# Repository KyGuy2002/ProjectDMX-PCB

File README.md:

PCB designs for projectdmx.us modular prop controller

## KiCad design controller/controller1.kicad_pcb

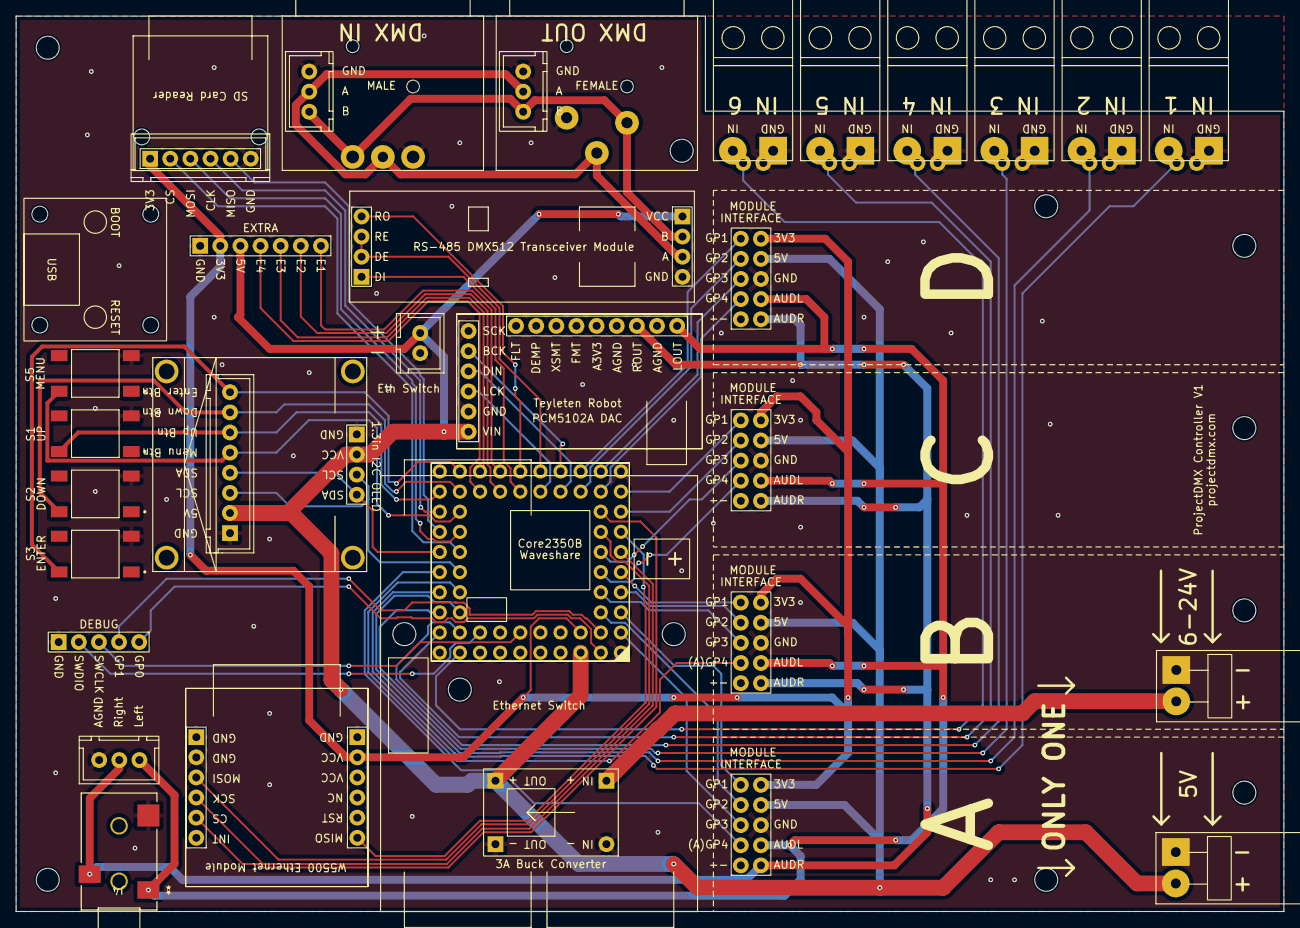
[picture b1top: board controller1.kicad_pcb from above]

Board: 2 copper layers, 160.0 x 113.0 mm, 31 parts (0 on the bottom side), 57 nets.

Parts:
J2: Female XLR Out; AC3FAH-AU-PRE_AMP
J3: Male XLR In; AC3MAH-AU-PRE_AMP
J4: SJ-3523-SMT; SJ-3523-SMT-TR
S1: UP; SW_TS04-66-43-BK-260-SMT
S2: DOWN; SW_TS04-66-43-BK-260-SMT
S3: ENTER; SW_TS04-66-43-BK-260-SMT
S5: MENU; SW_TS04-66-43-BK-260-SMT
U1: Waveshare RP2350B
U2: DMX Transceiver
U4: JST XH Power
U5: OLED 1_3in I2C
U6, U7, U13, U14: Module Interface
U8: Tey PCM DAC
U9: SD Card Reader
U10: W5500 Ethernet Module
U11: 3A Buck Converter
U12: Debug Header
U15, U17, U18, U19, U20, U21: Horiz Terminal Block
U16: Extra Header
U26: Interface Connector
U27, U28: DMX Alt JST
U29: Aux Alt JST

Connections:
3V3: U1.13 (3V3), U6.0, U7.0, U9.6 (3V3), U10.5 (3V3), U13.0, U14.0, U16.6 (3V)
5V: U1.3 (VBUS), U2.4 (VCC), U4.2 (GND), U5.3 (VCC), U6.4 (AGP4), U7.4 (AGP4), U8.6 (VIN), U11.1 (OUT_+), U13.4 (AGP4), U14.4 (AGP4), U16.5 (5V), U26.2 (5V)
GND: J2.1, J3.1, J4.2, S1.2, S2.2, S3.2, S5.2, U1.1 (GND), U1.10 (GND), U1.36 (GND), U1.55 (GND), U2.3 (GND), U4.1 (VCC), U5.4 (GND), U6.3 (GP3), U7.3 (GP3), U8.1 (SCK), U8.5 (GND), U9.1 (GND), U10.6 (GND), U10.11 (GND), U10.12 (GND), U11.2 (OUT_-), U11.4 (IN_-), U12.5 (GND), U13.3 (GP3), U14.3 (GP3), U15.2 (GND), U16.7 (GND), U17.2 (GND), U18.2 (GND), U19.2 (GND), U20.2 (GND), U21.2 (GND), U26.1 (GND), U27.1 (GND), U28.1 (GND), U29.1 (AGND)
GP7: U1.27 (GP7), U13.6 (5V)
unnamed: U1.62 (AGP40), U6.6 (5V)
unnamed: U1.64 (AGP41), U7.6 (5V)
unnamed: U1.65 (AGP42), U21.1 (IN)
unnamed: U1.67 (AGP43), U20.1 (IN)
unnamed: U1.66 (AGP44), U19.1 (IN)
unnamed: U1.20 (AGP45), U17.1 (IN)
unnamed: U1.19 (AGP46), U18.1 (IN)
unnamed: U1.9 (AGP47), U15.1 (IN)
unnamed: U1.2 (GP0), U12.1 (GP0)
unnamed: U1.12 (GP1), U12.2 (GP1)
unnamed: U1.11 (GP2), U6.7 (GND)
unnamed: U1.23 (GP3), U6.8
unnamed: U1.21 (GP4), U6.9
unnamed: U1.25 (GP5), U7.7 (GND)
unnamed: U1.24 (GP6), U7.8
unnamed: U1.26 (GP8), U7.9
unnamed: U1.29 (GP9), U13.7 (GND)
unnamed: U1.28 (GP10), U10.9 (SCLK)
unnamed: U1.31 (GP11), U10.10 (MOSI)
unnamed: U1.30 (GP12), U10.1 (MISO)
unnamed: U1.33 (GP13), U10.8 (CS)
unnamed: U1.32 (GP14), U13.8
unnamed: U1.34 (GP15), U13.9
unnamed: U1.35 (GP16), U14.6 (5V)
unnamed: U1.37 (GP17), U14.7 (GND)
unnamed: U1.38 (GP18), U14.8
unnamed: U1.39 (GP19), U14.9
unnamed: U1.41 (GP20), U8.3 (DIN)
unnamed: U1.40 (GP21), U8.2 (BCK)
unnamed: U1.42 (GP22), U8.4 (LCK)
unnamed: U1.44 (GP23), U2.2 (DE), U2.8 (RE)
unnamed: U1.46 (GP24), U2.1 (DI)
unnamed: U1.45 (GP25), U2.7 (RO)
unnamed: U1.48 (GP26), U16.2 (E2)
unnamed: U1.47 (GP27), U16.1 (E1)
unnamed: U1.49 (GP28), U16.4 (E4)
unnamed: U1.50 (GP29), U16.3 (E3)
unnamed: S3.3, U1.51 (GP30), U26.8 (Enter_Btn)
unnamed: S2.3, U1.52 (GP31), U26.7 (Down_Btn)
unnamed: S1.3, U1.53 (GP32), U26.6 (Up_Btn)
unnamed: S5.3, U1.56 (GP33), U26.5 (Menu_Btn)
unnamed: U1.57 (GP34), U9.3 (CLK)
unnamed: U1.59 (GP35), U9.4 (MOSI)
unnamed: U1.58 (GP36), U9.2 (MISO)
unnamed: U1.60 (GP37), U9.5 (CS)
unnamed: U1.61 (GP38), U5.1 (SDA), U26.4 (SDA)
unnamed: U1.63 (GP39), U5.2 (SCL), U26.3 (SCL)
unnamed: U1.16 (SWCLK), U12.3 (SWCLK)
unnamed: U1.18 (SWDIO), U12.4 (SWDIO)
unnamed: J2.3, J3.3, U2.5 (A), U27.2 (A), U28.2 (A)
unnamed: J2.2, J3.2, U2.6 (B), U27.3 (B), U28.3 (B)
unnamed: J4.1, U6.2 (GP2), U7.2 (GP2), U8.15 (LROUT), U13.2 (GP2), U14.2 (GP2), U29.3 (R)
unnamed: J4.3, U6.1 (GP1), U7.1 (GP1), U8.13 (ROUT), U13.1 (GP1), U14.1 (GP1), U29.2 (L)

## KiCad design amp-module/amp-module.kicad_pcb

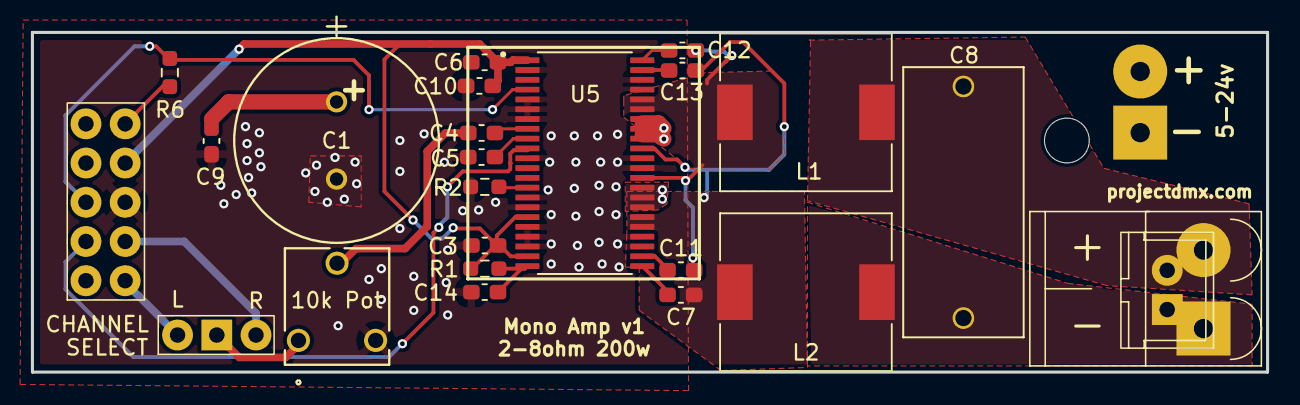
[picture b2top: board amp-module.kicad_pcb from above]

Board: 2 copper layers, 80.0 x 22.0 mm, 22 parts (0 on the bottom side), 16 nets.

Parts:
C1: 1000uf; 35YXJ1000M12.5X20
C3, C14: 1uF CER 25v; C_0603_1608Metric_Pad1.08x0.95mm_HandSolder
C4, C5: 10uF CER 25v; C_0603_1608Metric_Pad1.08x0.95mm_HandSolder
C6: 100nF; C_0603_1608Metric_Pad1.08x0.95mm_HandSolder
C7, C12, C13: 33nF CER 50v; C_0603_1608Metric_Pad1.08x0.95mm_HandSolder
C8: 1uf ECW Film; ECWFD2W105J
C9: 1uf GMK316BJ105KL 100v; C_0603_1608Metric_Pad1.08x0.95mm_HandSolder
C10: 10uF; C_0603_1608Metric_Pad1.08x0.95mm_HandSolder
C11: 33nf CER 50v; C_0603_1608Metric_Pad1.08x0.95mm_HandSolder
L1, L2: 7443331000
R1: 3.3Ω; R_0603_1608Metric_Pad0.98x0.95mm_HandSolder
R2: 30kΩ; R_0603_1608Metric_Pad0.98x0.95mm_HandSolder
R6: 10kΩ; R_0603_1608Metric_Pad0.98x0.95mm_HandSolder
U2: Vert Terminal Block p2
U3: 2p Output
U5: TPA3221DDVR; TPA3221
U6: PSU Select Jumper

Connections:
5V: C3.2, C6.2, C10.2, R1.1, U5.1 (VDD), U5.17 (CMUTE), U5.21 (AVDD)
GND: C1.2, C3.1, C5.2, C6.1, C9.2, C10.1, C14.1, R2.2, U5.2 (GAIN/SLV), U5.5 (GND-11), U5.6 (GND-5), U5.7 (GND-4), U5.11 (HEAD), U5.15 (IN2_P), U5.16 (IN2_M), U5.18 (GND-1), U5.19 (GND), U5.20 (GND-10), U5.25 (GND-6), U5.26 (GND-2), U5.33 (GND-3), U5.34 (GND-8), U5.41 (GND-9), U5.42 (GND-7)
unnamed: R6.2, U5.4 (FAULT)
unnamed: C8.2, L1.1, U2.1 (+), U3.1 (+)
unnamed: C8.1, L2.1, U2.2 (-), U3.2 (-)
unnamed: C13.1, U5.43 (BST1_M)
unnamed: C12.2, U5.44 (BST1_P)
unnamed: C7.2, U5.23 (BST2_M)
unnamed: C11.1, U5.24 (BST2_P)
unnamed: R2.1, U5.14 (FREQ_ADJ)
unnamed: C14.2, R1.2, U5.22 (GVDD)
unnamed: C5.1, U5.9 (IN1_M)
unnamed: C4.2, U5.8 (IN1_P)
unnamed: C7.1, C13.2, L2.2, U5.27 (OUT2_M), U5.28 (OUT2_M-1), U5.35 (OUT1_M)
unnamed: C11.2, C12.1, L1.2, U5.32 (OUT2_P), U5.39 (OUT1_P), U5.40 (OUT1_P-1)
VCC: C1.1, C9.1, U5.29 (PVDD-4), U5.30 (PVDD-5), U5.31 (PVDD-3), U5.36 (PVDD-2), U5.37 (PVDD-1), U5.38 (PVDD)

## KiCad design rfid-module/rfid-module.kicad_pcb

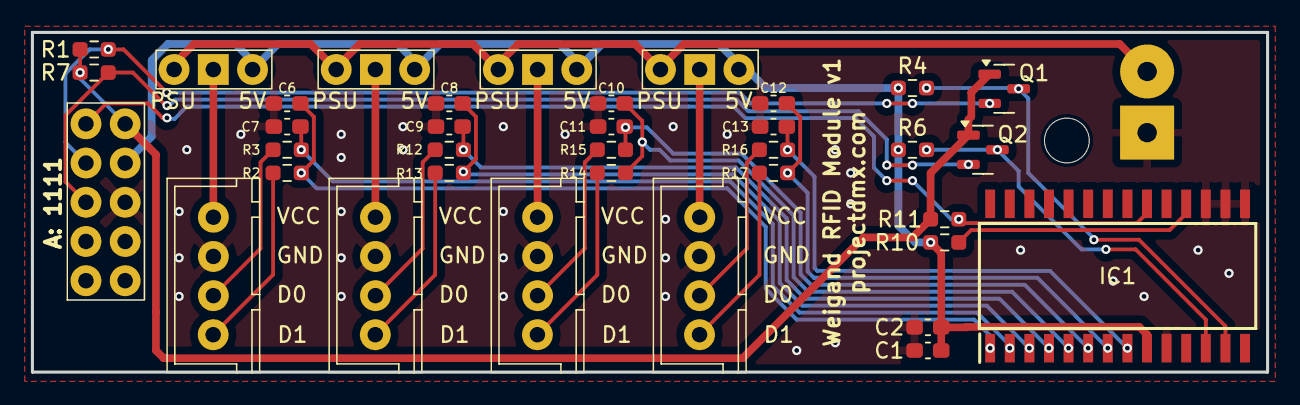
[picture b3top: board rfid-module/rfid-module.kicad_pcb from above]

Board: 2 copper layers, 80.0 x 22.0 mm, 35 parts (0 on the bottom side), 30 nets.

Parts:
C1: 100nF; C_0603_1608Metric_Pad1.08x0.95mm_HandSolder
C2: 10uF; C_0603_1608Metric_Pad1.08x0.95mm_HandSolder
C6, C7, C8, C9, C10, C11, C12, C13: 1nF; C_0603_1608Metric_Pad1.08x0.95mm_HandSolder
IC1: MCP23017-E_SO; MCP23017
Q1, Q2: BSS138; SOT-23
R1, R4, R6, R7, R11: 4.7kΩ; R_0603_1608Metric_Pad0.98x0.95mm_HandSolder
R2, R3, R12, R13, R14, R15, R16, R17: 1kΩ; R_0603_1608Metric_Pad0.98x0.95mm_HandSolder
R10: 10kΩ; R_0603_1608Metric_Pad0.98x0.95mm_HandSolder
U2, U5, U7, U9: RFID JST
U3, U4, U6, U8: RFID PSU Select

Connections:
3V3: Q1.1 (G), Q2.1 (G), R1.1, R7.1, R11.1
5V: C1.2, C2.2, IC1.9 (VDD), R4.1, R6.1, R10.1, U3.1 (5V), U4.1 (5V), U6.1 (5V), U8.1 (5V)
12V: U3.3 (PSU), U4.3 (PSU), U6.3 (PSU), U8.3 (PSU)
GND: C1.1, C2.1, C6.1, C7.1, C8.1, C9.1, C10.1, C11.1, C12.1, C13.1, IC1.10 (VSS), IC1.15 (A0), IC1.16 (A1), IC1.17 (A2), U2.2 (GND), U5.2 (GND), U7.2 (GND), U9.2 (GND)
unnamed: C6.2, IC1.1 (GPB0), R2.2
unnamed: C7.2, IC1.2 (GPB1), R3.2
unnamed: C8.2, IC1.3 (GPB2), R13.2
unnamed: C9.2, IC1.4 (GPB3), R12.2
unnamed: C10.2, IC1.5 (GPB4), R14.2
unnamed: C11.2, IC1.6 (GPB5), R15.2
unnamed: C12.2, IC1.7 (GPB6), R17.2
unnamed: C13.2, IC1.8 (GPB7), R16.2
unnamed: IC1.20 (INTA), R11.2
unnamed: IC1.12 (SCL), Q2.3 (D), R6.2
unnamed: IC1.13 (SDA), Q1.3 (D), R4.2
unnamed: IC1.18 (~RESET), R10.2
unnamed: Q1.2 (S), R1.2
unnamed: Q2.2 (S), R7.2
unnamed: R3.1, U2.3 (D0)
unnamed: R2.1, U2.4 (D1)
unnamed: U2.1 (VCC), U3.2 (OUT)
unnamed: U4.2 (OUT), U5.1 (VCC)
unnamed: R12.1, U5.3 (D0)
unnamed: R13.1, U5.4 (D1)
unnamed: U6.2 (OUT), U7.1 (VCC)
unnamed: R15.1, U7.3 (D0)
unnamed: R14.1, U7.4 (D1)
unnamed: U8.2 (OUT), U9.1 (VCC)
unnamed: R16.1, U9.3 (D0)
unnamed: R17.1, U9.4 (D1)

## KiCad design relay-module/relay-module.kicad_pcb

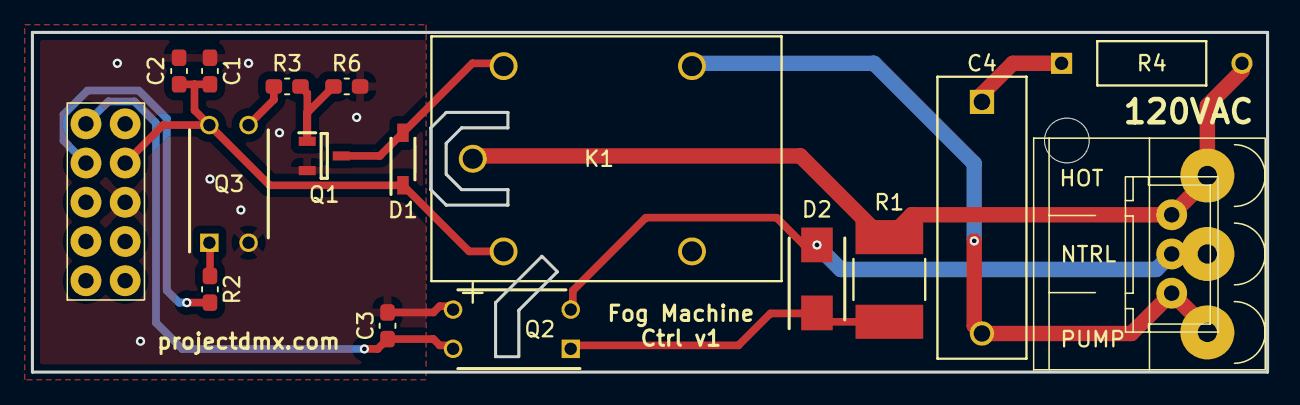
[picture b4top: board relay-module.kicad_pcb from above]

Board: 2 copper layers, 80.0 x 22.0 mm, 17 parts (0 on the bottom side), 12 nets.

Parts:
C1: 100nF; C_0603_1608Metric_Pad1.08x0.95mm_HandSolder
C2, C3: 10uF; C_0603_1608Metric_Pad1.08x0.95mm_HandSolder
C4: C; PHE840EB6100KB05R17
D1: M7; 1N4148W
D2: M7; S1M
K1: SRD-05VDC-SL-C; G5LE_14_DC5
Q1: SOT95P240X115-3N; S8050
Q2, Q3: DIP762W60P254L460H450Q4N; PC817X2NSZ9F
R1: 47kΩ; 354047KFT
R2: 220Ω; C_0603_1608Metric_Pad1.08x0.95mm_HandSolder
R3: 1kΩ; C_0603_1608Metric_Pad1.08x0.95mm_HandSolder
R4: R; FMP100JR-52-100R
R6: 10kΩ; C_0603_1608Metric_Pad1.08x0.95mm_HandSolder
U2: Vert Terminal Block p3
U4: DMX Alt JST

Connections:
5V: C1.2, C2.2, D1.1, K1.2 (C1), Q3.4 (COLLECTOR)
GND: C1.1, C2.1, C3.2, Q1.2 (E), Q2.3 (EMITTER), Q3.2 (CATHODE), R6.1
unnamed: C4.1, R4.1
unnamed: D1.2, K1.5 (NC), Q1.3 (C)
unnamed: K1.1 (COM), R1.1, R4.2, U2.1 (Hot), U4.3 (Hot)
unnamed: C4.2, K1.4 (NO), U2.3 (Pump), U4.1 (Pump)
unnamed: Q1.1 (B), R3.1, R6.2
unnamed: D2.1, Q2.1 (ANODE), R1.2
unnamed: D2.2, Q2.2 (CATHODE), U2.2 (Neutral), U4.2 (Neutral)
unnamed: C3.1, Q2.4 (COLLECTOR)
unnamed: Q3.1 (ANODE), R2.1
unnamed: Q3.3 (EMITTER), R3.2

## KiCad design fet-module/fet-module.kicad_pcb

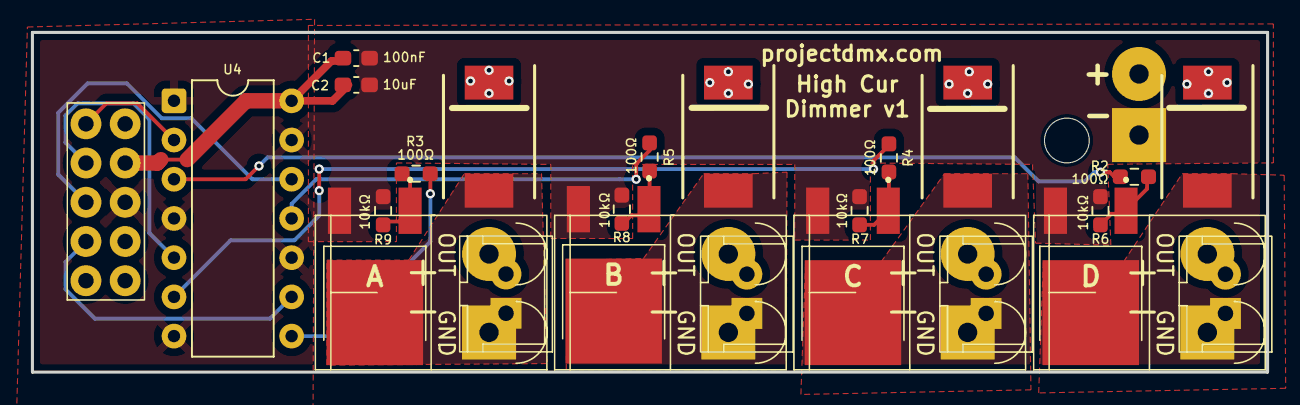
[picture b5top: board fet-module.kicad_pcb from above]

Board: 2 copper layers, 80.0 x 22.0 mm, 27 parts (0 on the bottom side), 11 nets.

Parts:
A: SK1045; SK1045-LTP
A#2: AOD4184A; AOD4185A
B: SK1045; SK1045-LTP
B#2: AOD4184A; AOD4185A
C: AOD4184A; AOD4185A
C1: 100nF; C_0603_1608Metric_Pad1.08x0.95mm_HandSolder
C2: 10uF; C_0603_1608Metric_Pad1.08x0.95mm_HandSolder
C#2: SK1045; SK1045-LTP
D: SK1045; SK1045-LTP
D#2: AOD4184A; AOD4185A
R2, R3, R4, R5: 100Ω; R_0603_1608Metric_Pad0.98x0.95mm_HandSolder
R6, R7, R8, R9: 10kΩ; R_0603_1608Metric_Pad0.98x0.95mm_HandSolder
U1, U6, U8, U10: JST XH Power
U2, U3, U7, U9: Vert Terminal Block p2
U4: DIP-14_W7.62mm

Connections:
5V: C1.2, C2.2, U4.14 (VCC)
GND: A#2.3 (S), B#2.3 (S), C.3 (S), C1.1, C2.1, D#2.3 (S), R6.1, R7.1, R8.1, R9.1, U4.1 (1_OE), U4.4 (2_OE), U4.7 (3_OE), U4.10 (4_OE), U4.13 (GND)
HIGH-A: A.2, A#2.2 (D), U7.2 (-), U8.1 (+)
HIGH-B: B.2, B#2.2 (D), U3.2 (-), U6.1 (+)
HIGH-C: C.2 (D), C#2.2, U1.1 (+), U2.2 (-)
HIGH-D: D.2, D#2.2 (D), U9.2 (-), U10.1 (+)
unnamed: D#2.1 (G), R2.1, R2.2, R6.2, U4.3 (1Y_(Out))
unnamed: A#2.1 (G), R3.1, R3.2, R9.2, U4.8 (3A_(In))
unnamed: C.1 (G), R4.1, R4.2, R7.2, U4.6 (2Y_(Out))
unnamed: B#2.1 (G), R5.1, R5.2, R8.2, U4.11 (4A_(In))
VCC: A.1, B.1, C#2.1, D.1, U1.2 (-), U2.1 (+), U3.1 (+), U6.2 (-), U7.1 (+), U8.2 (-), U9.1 (+), U10.2 (-)

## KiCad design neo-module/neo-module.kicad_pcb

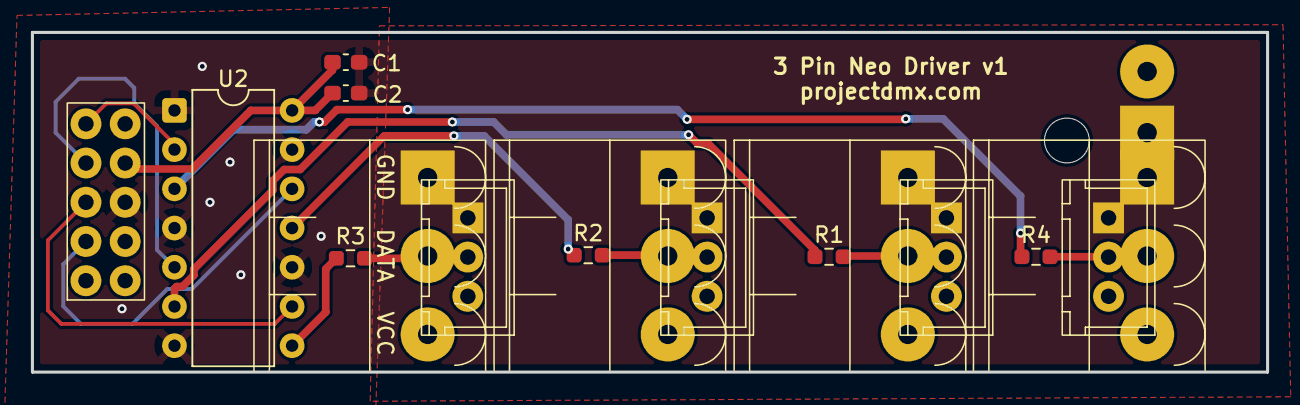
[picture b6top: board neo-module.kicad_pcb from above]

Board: 2 copper layers, 80.0 x 22.0 mm, 7 parts (0 on the bottom side), 6 nets.

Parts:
C1: 100nF; C_0603_1608Metric_Pad1.08x0.95mm_HandSolder
C2: 10uF; C_0603_1608Metric_Pad1.08x0.95mm_HandSolder
R1, R2, R3, R4: 330Ω; R_0603_1608Metric_Pad0.98x0.95mm_HandSolder
U2: DIP-14_W7.62mm

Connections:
5V: C1.2, C2.2, U2.14 (VCC)
GND: C1.1, C2.1, U2.1 (1_OE), U2.4 (2_OE), U2.7 (3_OE), U2.10 (4_OE), U2.13 (GND)
unnamed: R3.1, R3.2, U2.8 (3A_(In))
unnamed: R2.1, R2.2, U2.11 (4A_(In))
unnamed: R1.1, R1.2, U2.6 (2Y_(Out))
unnamed: R4.1, R4.2, U2.3 (1Y_(Out))

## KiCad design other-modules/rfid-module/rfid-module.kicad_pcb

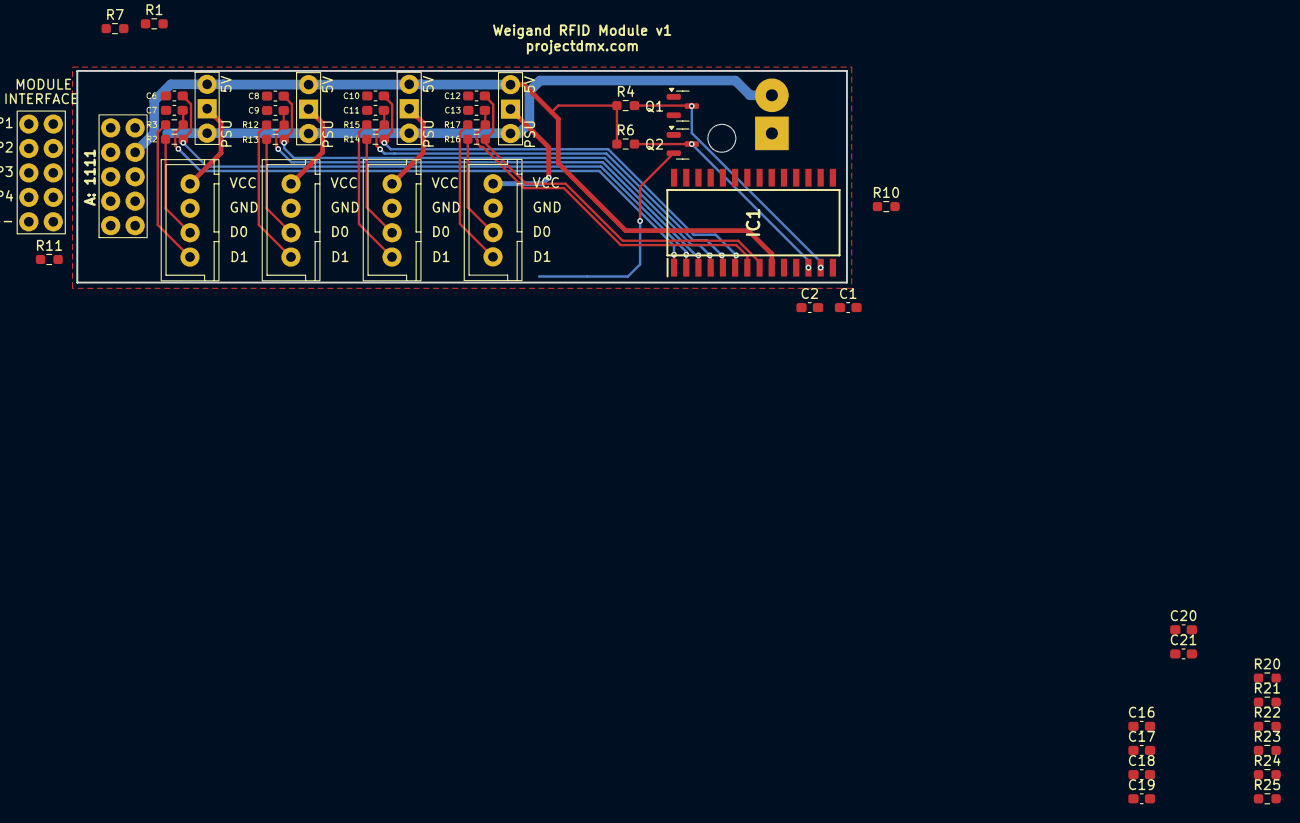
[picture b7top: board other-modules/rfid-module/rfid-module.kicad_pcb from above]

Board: 2 copper layers, 80.0 x 22.0 mm, 48 parts (0 on the bottom side), 36 nets.

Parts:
C1: 100nF; C_0603_1608Metric_Pad1.08x0.95mm_HandSolder
C2: 10uF; C_0603_1608Metric_Pad1.08x0.95mm_HandSolder
C6, C7, C8, C9, C10, C11, C12, C13, C16, C17, C18, C19, C20, C21: 1nF; C_0603_1608Metric_Pad1.08x0.95mm_HandSolder
IC1: MCP23017-E_SO; MCP23017
Q1, Q2: BSS138; SOT-23
R1, R4, R6, R7, R11: 4.7kΩ; R_0603_1608Metric_Pad0.98x0.95mm_HandSolder
R2, R3, R12, R13, R14, R15, R16, R17, R20, R21, R22, R23, R24, R25: 1kΩ; R_0603_1608Metric_Pad0.98x0.95mm_HandSolder
R10: 10kΩ; R_0603_1608Metric_Pad0.98x0.95mm_HandSolder
U1: Module Interface
U2, U5, U7, U9: RFID JST
U3, U4, U6, U8: RFID PSU Select

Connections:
3V3: Q1.1 (G), Q2.1 (G), R1.1, R7.1, R11.1
5V: C1.2, C2.2, IC1.9 (VDD), R4.1, R6.1, R10.1, U1.6 (5V), U3.1 (5V), U4.1 (5V), U6.1 (5V), U8.1 (5V)
12V: U3.3 (PSU), U4.3 (PSU), U6.3 (PSU), U8.3 (PSU)
GND: C1.1, C2.1, C6.1, C7.1, C8.1, C9.1, C10.1, C11.1, C12.1, C13.1, C16.1, C17.1, C18.1, C19.1, C20.1, C21.1, IC1.10 (VSS), IC1.15 (A0), IC1.16 (A1), IC1.17 (A2), U1.7 (GND), U2.2 (GND), U5.2 (GND), U7.2 (GND), U9.2 (GND)
unnamed: C21.2, IC1.21 (GPA0), R25.2
unnamed: C20.2, IC1.22 (GPA1), R24.2
unnamed: C19.2, IC1.23 (GPA2), R23.2
unnamed: C18.2, IC1.24 (GPA3), R22.2
unnamed: C17.2, IC1.25 (GPA4), R21.2
unnamed: C16.2, IC1.26 (GPA5), R20.2
unnamed: C7.2, IC1.1 (GPB0), R3.2
unnamed: C6.2, IC1.2 (GPB1), R2.2
unnamed: C9.2, IC1.3 (GPB2), R12.2
unnamed: C8.2, IC1.4 (GPB3), R13.2
unnamed: C11.2, IC1.5 (GPB4), R15.2
unnamed: C10.2, IC1.6 (GPB5), R14.2
unnamed: C13.2, IC1.7 (GPB6), R17.2
unnamed: C12.2, IC1.8 (GPB7), R16.2
unnamed: IC1.20 (INTA), R11.2, U1.1 (GP1)
unnamed: IC1.12 (SCL), Q2.3 (D), R6.2
unnamed: IC1.13 (SDA), Q1.3 (D), R4.2
unnamed: IC1.18 (~RESET), R10.2
unnamed: Q1.2 (S), R1.2, U1.2 (GP2)
unnamed: Q2.2 (S), R7.2, U1.3 (GP3)
unnamed: R2.1, U2.3 (D0)
unnamed: R3.1, U2.4 (D1)
unnamed: U2.1 (VCC), U3.2 (OUT)
unnamed: U4.2 (OUT), U5.1 (VCC)
unnamed: R13.1, U5.3 (D0)
unnamed: R12.1, U5.4 (D1)
unnamed: U6.2 (OUT), U7.1 (VCC)
unnamed: R14.1, U7.3 (D0)
unnamed: R15.1, U7.4 (D1)
unnamed: U8.2 (OUT), U9.1 (VCC)
unnamed: R16.1, U9.3 (D0)
unnamed: R17.1, U9.4 (D1)

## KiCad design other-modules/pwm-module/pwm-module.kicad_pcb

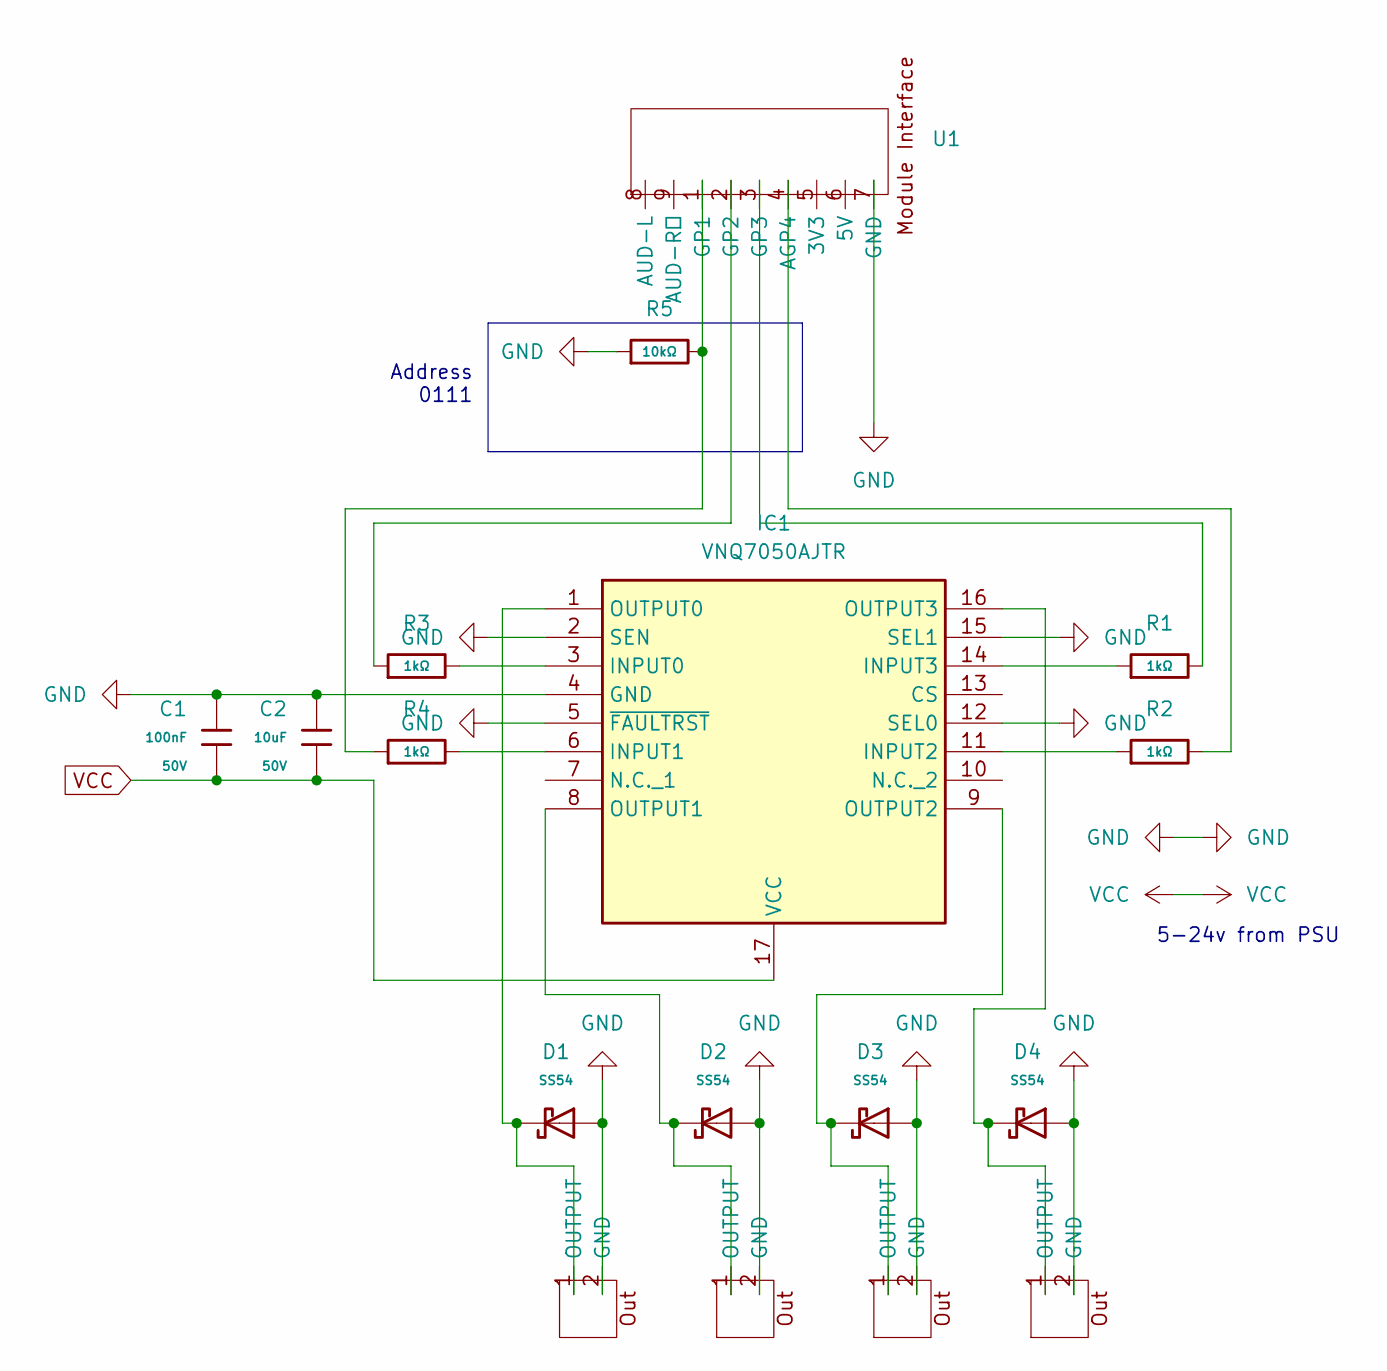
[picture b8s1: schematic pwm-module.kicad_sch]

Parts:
C1: 100nF; C_0402; Voltage Rated 50V; Tolerance ±10%; Part CL05B104KO5NNNC; LCSC C1525
C2: 10uF; C_0402; Voltage Rated 50V; Tolerance ±20%; Part CL05A106MQ5NUNC; LCSC C15525
D1, D2, D3, D4: SS54; D_SMA; Forward Voltage (Vf@If) 550mV@5A; Reverse Voltage (Vr) 40V; Part SS54; LCSC C22452
IC1: VNQ7050AJTR; Manufacturer_Part_Number VNQ7050AJTR; Mouser Part Number 511-VNQ7050AJTR
R1, R2, R3, R4: 1kΩ; R_0402; Overload Voltage (Max) 50V; Tolerance ±1%; Part 0402WGF1001TCE; LCSC C11702
R5: 10kΩ; R_0402; Overload Voltage (Max) 50V; Tolerance ±1%; Part 0402WGF1002TCE; LCSC C25744
U1: Module Interface
U2, U3, U4, U5: 2p Output

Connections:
GND: C1.1, C2.1, D1.2, D2.2, D3.2, D4.2, IC1.2 (SEN), IC1.4 (GND), IC1.5 (~FAULTRST), IC1.12 (SEL0), IC1.15 (SEL1), R5.1, U1.7 (GND), U2.2 (GND), U3.2 (GND), U4.2 (GND), U5.2 (GND)
unnamed: IC1.3 (INPUT0), R3.2
unnamed: IC1.6 (INPUT1), R4.2
unnamed: IC1.11 (INPUT2), R2.1
unnamed: IC1.14 (INPUT3), R1.1
unnamed: D1.1, IC1.1 (OUTPUT0), U2.1 (OUTPUT)
unnamed: D2.1, IC1.8 (OUTPUT1), U3.1 (OUTPUT)
unnamed: D3.1, IC1.9 (OUTPUT2), U4.1 (OUTPUT)
unnamed: D4.1, IC1.16 (OUTPUT3), U5.1 (OUTPUT)
unnamed: R2.2, U1.4 (AGP4)
unnamed: R4.1, R5.2, U1.1 (GP1)
unnamed: R3.1, U1.2 (GP2)
unnamed: R1.2, U1.3 (GP3)
VCC: C1.2, C2.2, IC1.17 (VCC)

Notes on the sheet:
Address 0111
5-24v from PSU

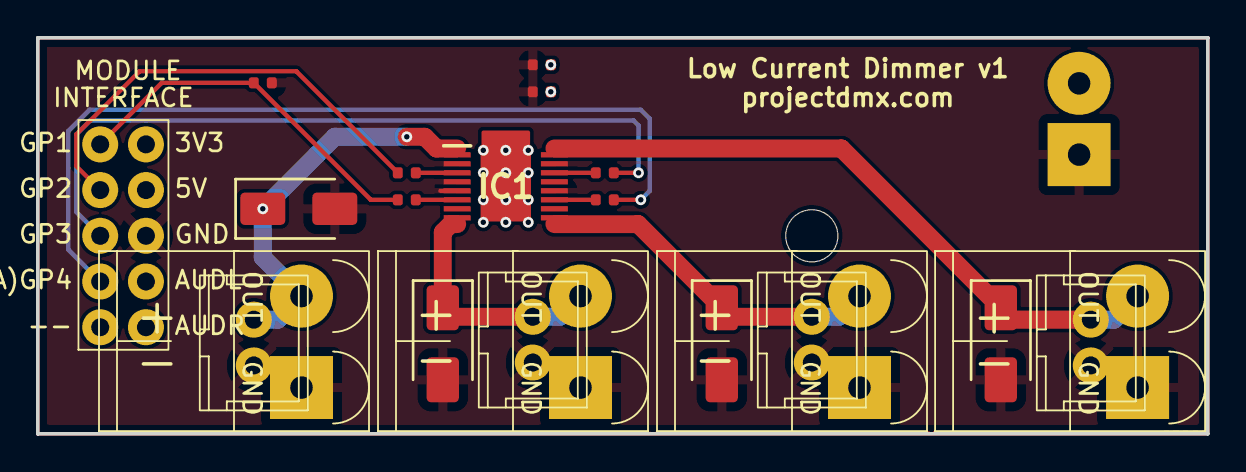
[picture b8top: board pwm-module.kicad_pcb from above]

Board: 2 copper layers, 65.0 x 22.0 mm, 16 parts (0 on the bottom side), 11 nets.

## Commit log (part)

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2026-04-26 move input jst alt pins closer to overlap term pins
2026-04-27 move mounting holes on modules and controller
2026-04-27 adjust footprints and cleanup stuff
2026-04-27 update footprints on neo module
2026-04-28 cleanup footprints and layout
2026-04-28 update 3d models
2026-04-28 add fog relay module
2026-05-01 finish relay + start rfid
2026-05-01 finish everything
2026-05-04 small changes
2026-05-04 replace amp with screw pot
2026-05-05 update fill
